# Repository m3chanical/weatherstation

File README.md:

#  ESP32 Weather Station

This project uses the weather station kit available from [Spark Fun](https://www.sparkfun.com/products/15901) connected to an ESP32 module from [Adafruit](https://www.adafruit.com/product/3269).
The goal is to connect this to the sensors, battery, and solar panel inside of a weather proof box and transmit over MQTT to a LAN server. 

Use esp-idf. Follow instructions here: https://github.com/espressif/esp-idf

## Build

Create a `credentials.h` file in the `main/` directory with the appropriate wifi credentials.

`idf.py build`

## Flash

`idf.py -p <port> flash`

Port should be the device path of the usb device. e.g. `/dev/ttyUSB0`

## Monitor

`idf.py -p <port> monitor`

## MQTT

On the dev branch is a test set up for MQTT hardcoded to a MQTT server on my LAN. I'll break it out into `credentials.h` but for now this will do.
It subscribes to `/topic/qos0` (from protocols/mqtt example from esp-idf) and can be tested with the following:
```
# Publish:
mosquitto_pub -h <ip> -p <port> -t /topic/qos0 -m "message"

# Subscribe:
# This will subscribe to all topics for debugging
mosquitto_sub -v -h <ip> -p <port> -t '#'
```

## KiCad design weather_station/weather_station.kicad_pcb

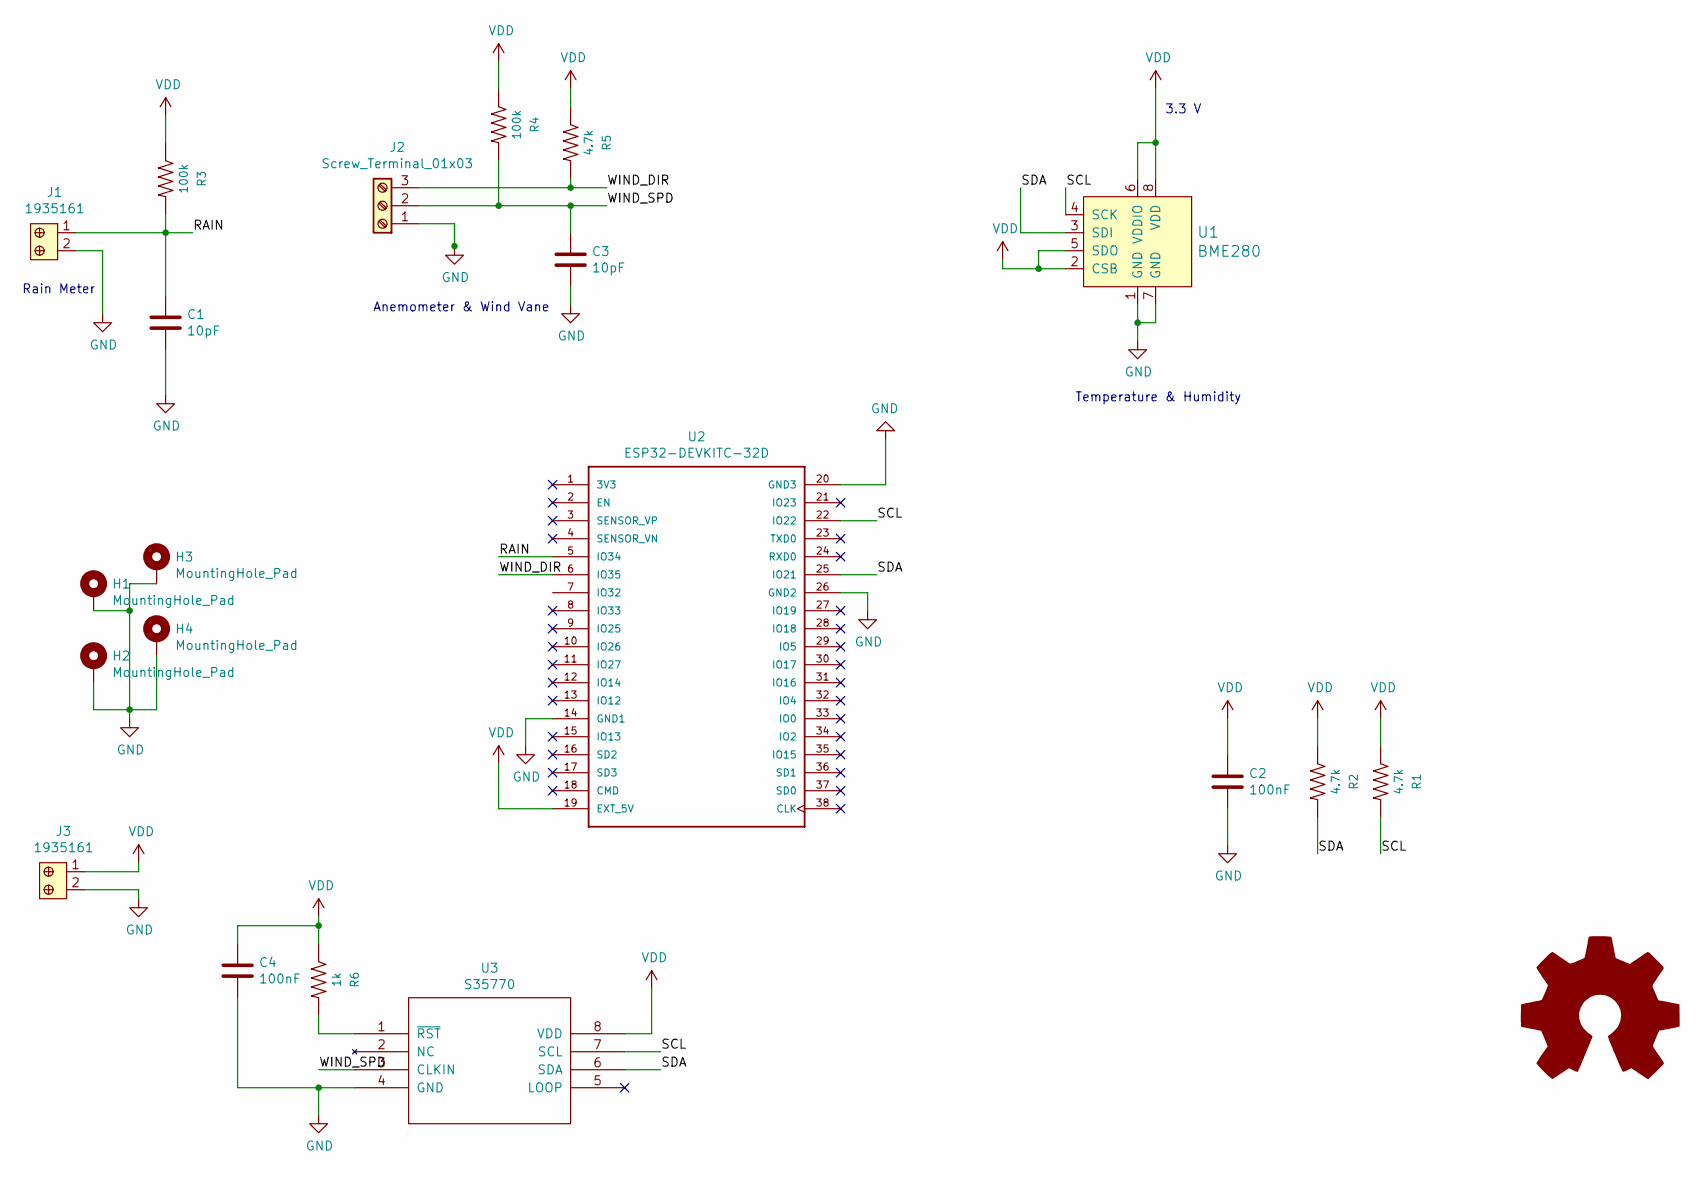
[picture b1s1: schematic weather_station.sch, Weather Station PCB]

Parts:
C1, C3: 10pF; C_0603_1608Metric_Pad1.08x0.95mm_HandSolder
C2, C4: 100nF; C_0603_1608Metric_Pad1.08x0.95mm_HandSolder
H1, H2, H3, H4: MountingHole_Pad; MountingHole_3.2mm_M3_Pad
J1, J3: 1935161; TerminalBlock_Phoenix_MKDS-1,5-2_1x02_P5.00mm_Horizontal; MPN 1935161; Digi-Key_PN 277-1667-ND
J2: Screw_Terminal_01x03; TerminalBlock_Phoenix_MKDS-1,5-3_1x03_P5.00mm_Horizontal
R1, R2, R5: 4.7k; R_0603_1608Metric_Pad0.98x0.95mm_HandSolder
R3, R4: 100k; R_0603_1608Metric_Pad0.98x0.95mm_HandSolder
R6: 1k; R_0603_1608Metric_Pad0.98x0.95mm_HandSolder
U1: BME280; Pressure_Sensor_LGA-8_2.5x2.5mm_BME280; MPN BME280; Digi-Key_PN 828-1063-1-ND
U2: ESP32-DEVKITC-32D; MODULE_ESP32-DEVKITC-32D
U3: S35770; SSOP-8_5.25x5.24mm_P1.27mm

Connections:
/RAIN: C1.1, J1.1, R3.2, U2.5 (IO34)
/SCL: R1.2, U1.4 (SCK), U2.22 (IO22), U3.7 (SCL)
/SDA: R2.2, U1.3 (SDI), U2.25 (IO21), U3.6 (SDA)
/WIND_DIR: J2.3, R5.2, U2.6 (IO35)
/WIND_SPD: C3.1, J2.2, R4.2, U3.3 (CLKIN)
GND: C1.2, C2.2, C3.2, C4.2, H1.1, H2.1, H3.1, H4.1, J1.2, J2.1, J3.2, U1.1 (GND), U1.7 (GND), U2.14 (GND1), U2.20 (GND3), U2.26 (GND2), U3.4 (GND)
unnamed: R6.2, U3.1 (~RST)
VDD: C2.1, C4.1, J3.1, R1.1, R2.1, R3.1, R4.1, R5.1, R6.1, U1.2 (CSB), U1.5 (SDO), U1.6 (VDDIO), U1.8 (VDD), U2.19 (EXT_5V), U3.8 (VDD)

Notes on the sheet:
3.3 V
Rain Meter
Anemometer & Wind Vane
Temperature & Humidity

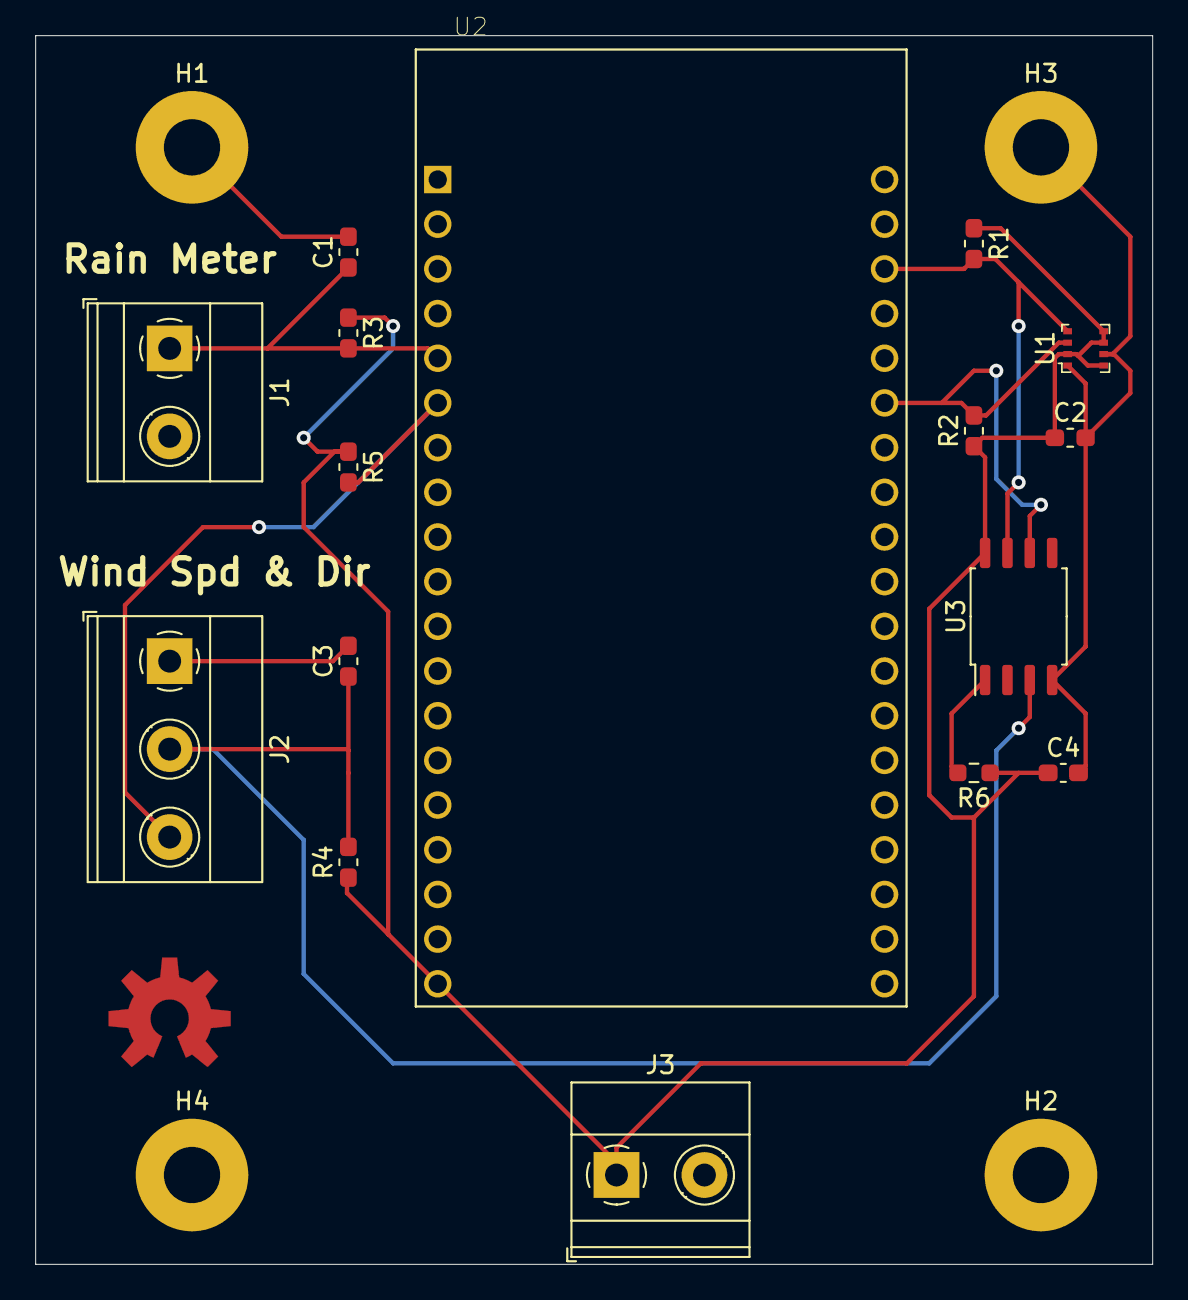
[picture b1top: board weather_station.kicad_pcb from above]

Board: 2 copper layers, 63.5 x 69.9 mm, 20 parts (0 on the bottom side), 8 nets.

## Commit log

2020-07-04 initial boilerplate add
2020-07-04 add esp-idf setup script [ UNTESTED ]
2020-07-25 update main, add pcb project files
2020-08-29 hardware update, add datasheets
2020-09-01 add bme280 template
2020-09-04 add bme280 interface
2020-09-05 schematic and pcb updates
2020-09-05 more pcb update
2021-03-13 add schematic pdf
2021-03-27 pcb updates, dont use this the schematic is scuffed
2021-03-27 stupid gitignore
2021-03-30 pcb updates and some tiny code changes
2021-03-30 Delete weather_station/gerbers directory
    don't need the stupid gerbers in here. get out gerbers
2021-03-31 update pcb and add basic mqtt function
